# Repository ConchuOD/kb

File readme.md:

# Custom keyboard

Things that are sub-optimal:
- mounting holes are M2 when M3 would be better.
- SOD323 are needlessly small, requiring better soldering gear than is reasonable.

Thanks to Jorge Reyes for his simple T3.2 model: https://grabcad.com/library/teensy-3-1-3-2-1
Thanks also to Constantin for his eagle teensy models that I converted to use in kicad https://forum.pjrc.com/threads/24637-Updated-Teensy-3-1-and-Teensy-3-0-Eagle-libraries

After 2 years, I finally got myself a 3d printer. I might finally finish this :)

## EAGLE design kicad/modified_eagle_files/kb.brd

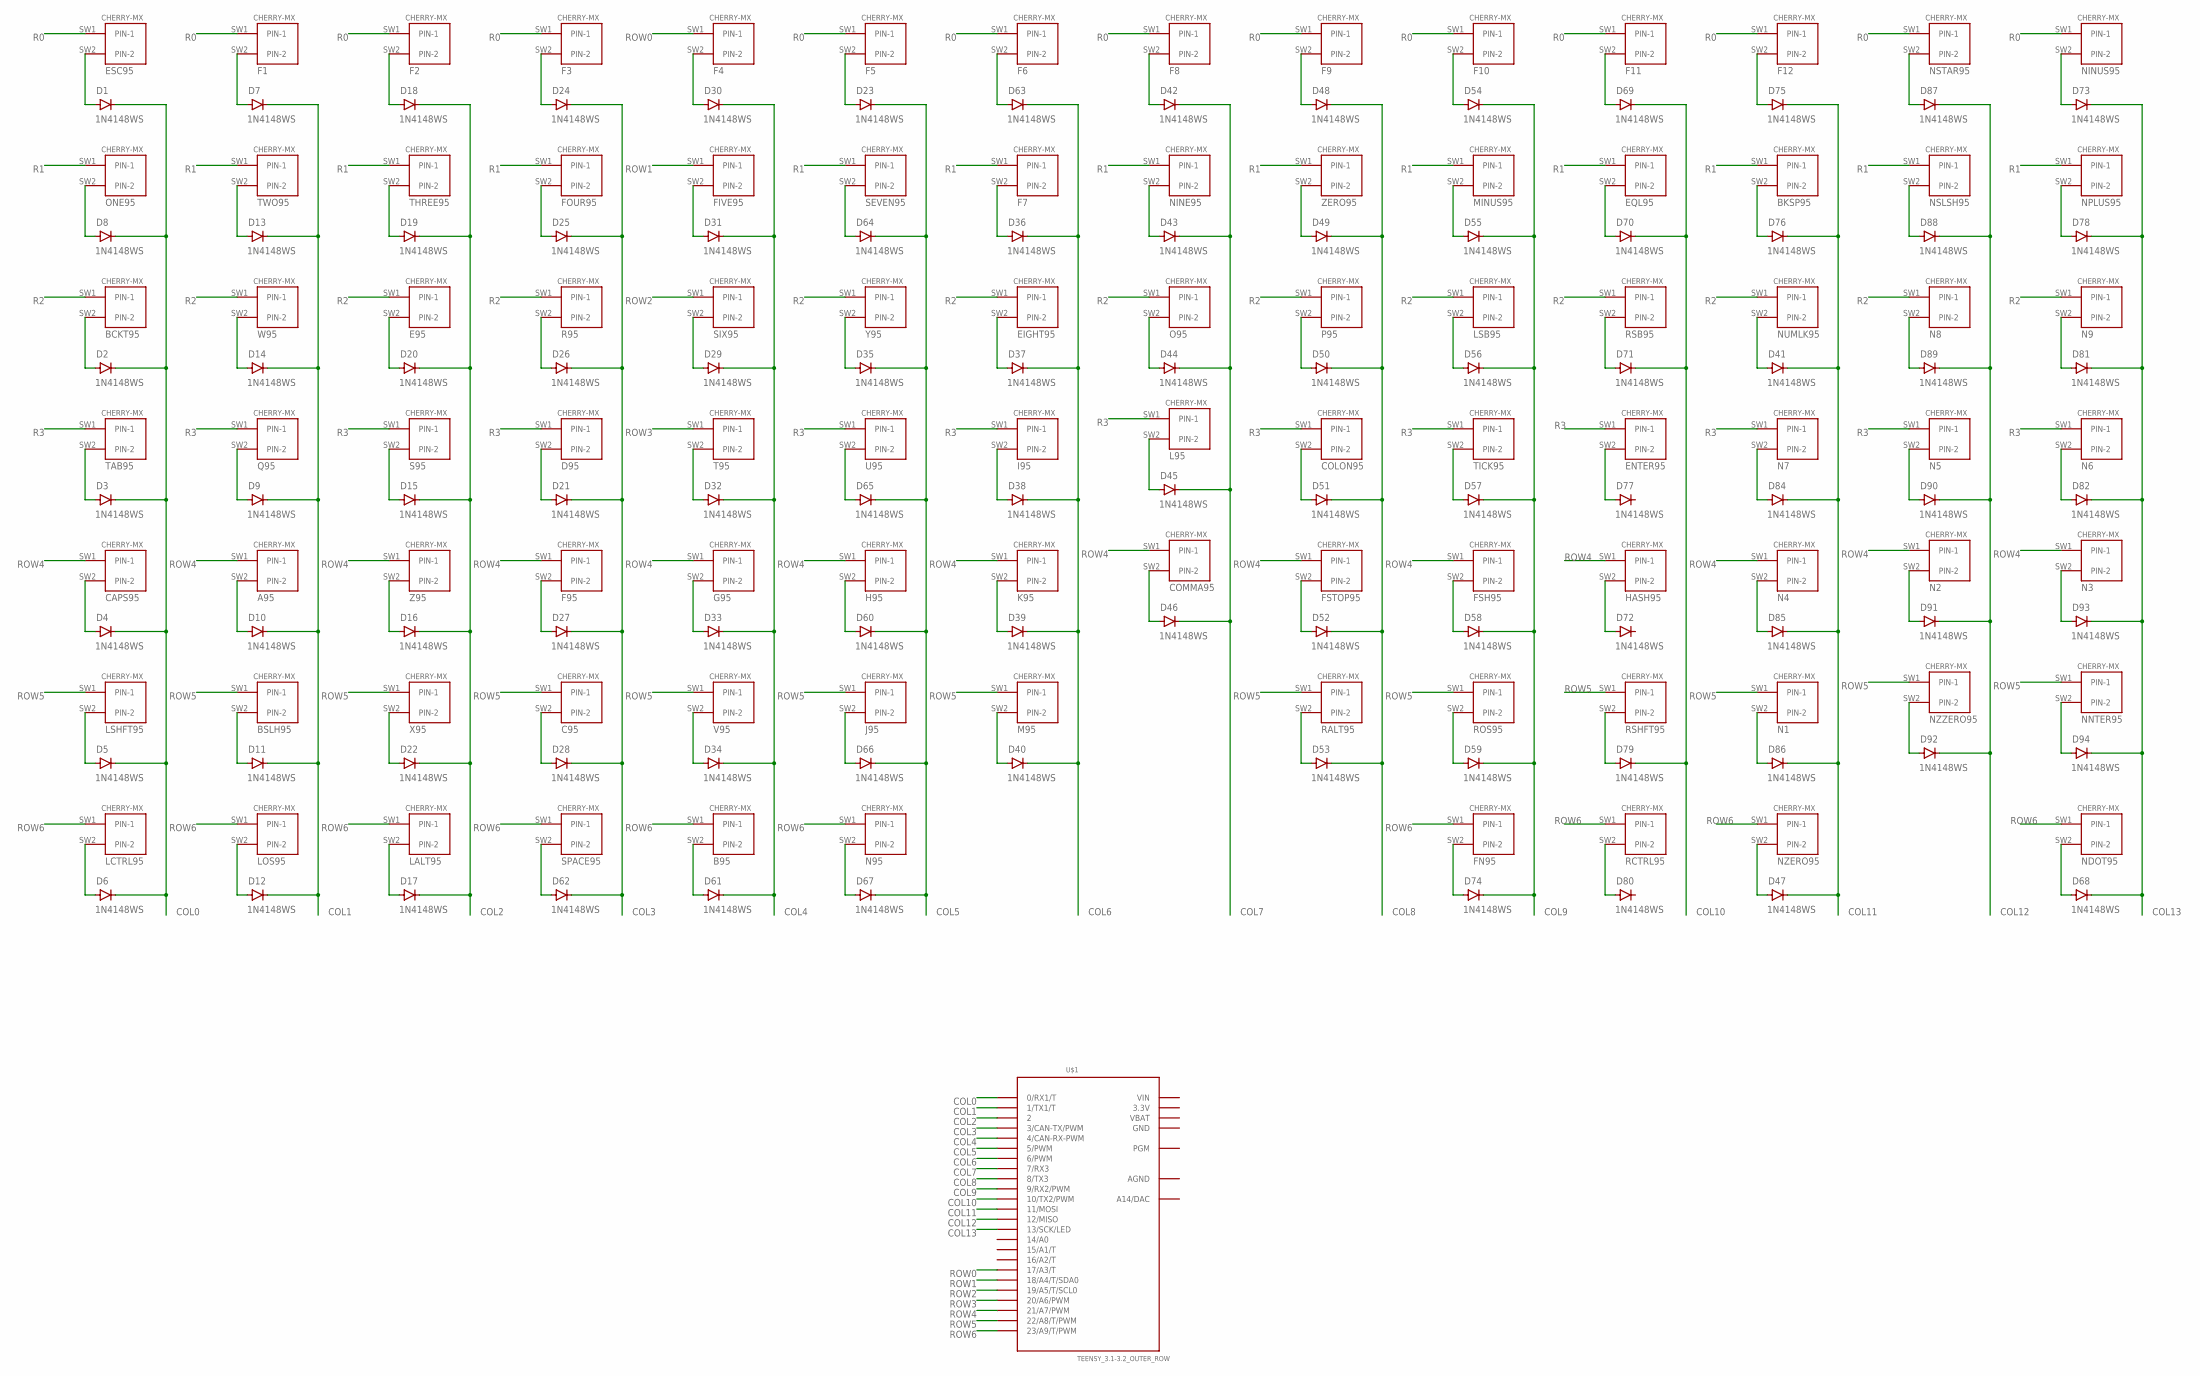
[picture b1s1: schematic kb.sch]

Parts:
A95: CHERRY-MX
B95: CHERRY-MX
BCKT95: CHERRY-MX
BKSP95: CHERRY-MX
BSLH95: CHERRY-MX
C95: CHERRY-MX
CAPS95: CHERRY-MX
COLON95: CHERRY-MX
COMMA95: CHERRY-MX
D1, D2, D3, D4, D5, D6, D7, D8, D9, D10, D11, D12, D13, D14, D15, D16, D17, D18, D19, D20, D21, D22, D23, D24, D25, D26, D27, D28, D29, D30, D31, D32, D33, D34, D35, D36, D37, D38, D39, D40, D41, D42, D43, D44, D45, D46, D47, D48, D49, D50, D51, D52, D53, D54, D55, D56, D57, D58, D59, D60, D61, D62, D63, D64, D65, D66, D67, D68, D69, D70, D71, D72, D73, D74, D75, D76, D77, D78, D79, D80, D81, D82, D84, D85, D86, D87, D88, D89, D90, D91, D92, D93, D94: 1N4148WS; SOD-323
D95: CHERRY-MX
E95: CHERRY-MX
EIGHT95: CHERRY-MX
ENTER95: CHERRY-MX
EQL95: CHERRY-MX
ESC95: CHERRY-MX
F1, F2, F3, F4, F5, F6, F7, F8, F9, F10, F11, F12, F95: CHERRY-MX
FIVE95: CHERRY-MX
FN95: CHERRY-MX
FOUR95: CHERRY-MX
FSH95: CHERRY-MX
FSTOP95: CHERRY-MX
G95: CHERRY-MX
H95: CHERRY-MX
HASH95: CHERRY-MX
I95: CHERRY-MX
J95: CHERRY-MX
K95: CHERRY-MX
L95: CHERRY-MX
LALT95: CHERRY-MX
LCTRL95: CHERRY-MX
LOS95: CHERRY-MX
LSB95: CHERRY-MX
LSHFT95: CHERRY-MX
M95: CHERRY-MX
MINUS95: CHERRY-MX
N1, N2, N3, N4, N5, N6, N7, N8, N9, N95: CHERRY-MX
NDOT95: CHERRY-MX
NINE95: CHERRY-MX
NINUS95: CHERRY-MX
NNTER95: CHERRY-MX
NPLUS95: CHERRY-MX
NSLSH95: CHERRY-MX
NSTAR95: CHERRY-MX
NUMLK95: CHERRY-MX
NZERO95: CHERRY-MX
NZZERO95: CHERRY-MX
O95: CHERRY-MX
ONE95: CHERRY-MX
P95: CHERRY-MX
Q95: CHERRY-MX
R95: CHERRY-MX
RALT95: CHERRY-MX
RCTRL95: CHERRY-MX
ROS95: CHERRY-MX
RSB95: CHERRY-MX
RSHFT95: CHERRY-MX
S95: CHERRY-MX
SEVEN95: CHERRY-MX
SIX95: CHERRY-MX
SPACE95: CHERRY-MX
T95: CHERRY-MX
TAB95: CHERRY-MX
THREE95: CHERRY-MX
TICK95: CHERRY-MX
TWO95: CHERRY-MX
U95: CHERRY-MX
U$1: TEENSY_3.1-3.2_OUTER_ROW; TEENSY_3.0-3.2&LC_OUTER_ROW
V95: CHERRY-MX
W95: CHERRY-MX
X95: CHERRY-MX
Y95: CHERRY-MX
Z95: CHERRY-MX
ZERO95: CHERRY-MX

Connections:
3.3V: U$1.3.3V, U$1.3.3V1 (3.3V)
AGND: U$1.AGND
COL0: D1.C, D2.C, D3.C, D4.C, D5.C, D6.C, D8.C, U$1.0 (0/RX1/T)
COL1: D7.C, D9.C, D10.C, D11.C, D12.C, D13.C, D14.C, U$1.1 (1/TX1/T)
COL2: D15.C, D16.C, D17.C, D18.C, D19.C, D20.C, D22.C, U$1.2
COL3: D21.C, D24.C, D25.C, D26.C, D27.C, D28.C, D62.C, U$1.3 (3/CAN-TX/PWM)
COL4: D29.C, D30.C, D31.C, D32.C, D33.C, D34.C, D61.C, U$1.4 (4/CAN-RX-PWM)
COL5: D23.C, D35.C, D60.C, D64.C, D65.C, D66.C, D67.C, U$1.5 (5/PWM)
COL6: D36.C, D37.C, D38.C, D39.C, D40.C, D63.C, U$1.6 (6/PWM)
COL7: D42.C, D43.C, D44.C, D45.C, D46.C, U$1.7 (7/RX3)
COL8: D48.C, D49.C, D50.C, D51.C, D52.C, D53.C, U$1.8 (8/TX3)
COL9: D54.C, D55.C, D56.C, D57.C, D58.C, D59.C, D74.C, U$1.9 (9/RX2/PWM)
COL10: D69.C, D70.C, D71.C, D79.C, U$1.10 (10/TX2/PWM)
COL11: D41.C, D47.C, D75.C, D76.C, D84.C, D85.C, D86.C, U$1.11 (11/MOSI)
COL12: D87.C, D88.C, D89.C, D90.C, D91.C, D92.C, U$1.12 (12/MISO)
COL13: D68.C, D73.C, D78.C, D81.C, D82.C, D93.C, D94.C, U$1.13 (13/SCK/LED)
GND: U$1.GND, U$1.GND1 (GND)
unnamed: D1.A, ESC95.SW2 (PIN-2)
unnamed: BCKT95.SW2 (PIN-2), D2.A
unnamed: D3.A, TAB95.SW2 (PIN-2)
unnamed: CAPS95.SW2 (PIN-2), D4.A
unnamed: D5.A, LSHFT95.SW2 (PIN-2)
unnamed: D6.A, LCTRL95.SW2 (PIN-2)
unnamed: D8.A, ONE95.SW2 (PIN-2)
unnamed: D9.A, Q95.SW2 (PIN-2)
unnamed: A95.SW2 (PIN-2), D10.A
unnamed: BSLH95.SW2 (PIN-2), D11.A
unnamed: D12.A, LOS95.SW2 (PIN-2)
unnamed: D13.A, TWO95.SW2 (PIN-2)
unnamed: D14.A, W95.SW2 (PIN-2)
unnamed: D15.A, S95.SW2 (PIN-2)
unnamed: D16.A, Z95.SW2 (PIN-2)
unnamed: D17.A, LALT95.SW2 (PIN-2)
unnamed: D7.A, F1.SW2 (PIN-2)
unnamed: D19.A, THREE95.SW2 (PIN-2)
unnamed: D20.A, E95.SW2 (PIN-2)
unnamed: D21.A, D95.SW2 (PIN-2)
unnamed: D22.A, X95.SW2 (PIN-2)
unnamed: D29.A, SIX95.SW2 (PIN-2)
unnamed: D18.A, F2.SW2 (PIN-2)
unnamed: D25.A, FOUR95.SW2 (PIN-2)
unnamed: D26.A, R95.SW2 (PIN-2)
unnamed: D27.A, F95.SW2 (PIN-2)
unnamed: C95.SW2 (PIN-2), D28.A
unnamed: D35.A, Y95.SW2 (PIN-2)
unnamed: D24.A, F3.SW2 (PIN-2)
unnamed: D31.A, FIVE95.SW2 (PIN-2)
unnamed: D32.A, T95.SW2 (PIN-2)
unnamed: D33.A, G95.SW2 (PIN-2)
unnamed: D34.A, V95.SW2 (PIN-2)
unnamed: D60.A, H95.SW2 (PIN-2)
unnamed: D30.A, F4.SW2 (PIN-2)
unnamed: D37.A, EIGHT95.SW2 (PIN-2)
unnamed: D38.A, I95.SW2 (PIN-2)
unnamed: D39.A, K95.SW2 (PIN-2)
unnamed: D40.A, M95.SW2 (PIN-2)
unnamed: D41.A, NUMLK95.SW2 (PIN-2)
unnamed: D36.A, F7.SW2 (PIN-2)
unnamed: D43.A, NINE95.SW2 (PIN-2)
unnamed: D44.A, O95.SW2 (PIN-2)
unnamed: D45.A, L95.SW2 (PIN-2)
unnamed: COMMA95.SW2 (PIN-2), D46.A
unnamed: D47.A, NZERO95.SW2 (PIN-2)
unnamed: D42.A, F8.SW2 (PIN-2)
unnamed: D49.A, ZERO95.SW2 (PIN-2)
unnamed: D50.A, P95.SW2 (PIN-2)
unnamed: COLON95.SW2 (PIN-2), D51.A
unnamed: D52.A, FSTOP95.SW2 (PIN-2)
unnamed: D53.A, RALT95.SW2 (PIN-2)
unnamed: D48.A, F9.SW2 (PIN-2)
unnamed: D55.A, MINUS95.SW2 (PIN-2)
unnamed: D56.A, LSB95.SW2 (PIN-2)
unnamed: D57.A, TICK95.SW2 (PIN-2)
unnamed: D58.A, FSH95.SW2 (PIN-2)
unnamed: D59.A, ROS95.SW2 (PIN-2)
unnamed: D54.A, F10.SW2 (PIN-2)
unnamed: B95.SW2 (PIN-2), D61.A
unnamed: D62.A, SPACE95.SW2 (PIN-2)
unnamed: D23.A, F5.SW2 (PIN-2)
unnamed: D64.A, SEVEN95.SW2 (PIN-2)
unnamed: D65.A, U95.SW2 (PIN-2)
unnamed: D66.A, J95.SW2 (PIN-2)
unnamed: D67.A, N95.SW2 (PIN-2)
unnamed: D68.A, NDOT95.SW2 (PIN-2)
unnamed: D63.A, F6.SW2 (PIN-2)
unnamed: D70.A, EQL95.SW2 (PIN-2)
unnamed: D71.A, RSB95.SW2 (PIN-2)
unnamed: D72.A, HASH95.SW2 (PIN-2)
unnamed: D78.A, NPLUS95.SW2 (PIN-2)
unnamed: D74.A, FN95.SW2 (PIN-2)
unnamed: D69.A, F11.SW2 (PIN-2)
unnamed: BKSP95.SW2 (PIN-2), D76.A
unnamed: D77.A, ENTER95.SW2 (PIN-2)
unnamed: D81.A, N9.SW2 (PIN-2)
unnamed: D79.A, RSHFT95.SW2 (PIN-2)
unnamed: D80.A, RCTRL95.SW2 (PIN-2)
unnamed: D75.A, F12.SW2 (PIN-2)
unnamed: D82.A, N6.SW2 (PIN-2)
unnamed: D84.A, N7.SW2 (PIN-2)
unnamed: D85.A, N4.SW2 (PIN-2)
unnamed: D86.A, N1.SW2 (PIN-2)
unnamed: D93.A, N3.SW2 (PIN-2)
unnamed: D88.A, NSLSH95.SW2 (PIN-2)
unnamed: D89.A, N8.SW2 (PIN-2)
unnamed: D90.A, N5.SW2 (PIN-2)
unnamed: D91.A, N2.SW2 (PIN-2)
unnamed: D92.A, NZZERO95.SW2 (PIN-2)
unnamed: D87.A, NSTAR95.SW2 (PIN-2)
unnamed: D94.A, NNTER95.SW2 (PIN-2)
unnamed: D73.A, NINUS95.SW2 (PIN-2)
R0: ESC95.SW1 (PIN-1), F1.SW1 (PIN-1), F2.SW1 (PIN-1), F3.SW1 (PIN-1), F5.SW1 (PIN-1), F6.SW1 (PIN-1), F8.SW1 (PIN-1), F9.SW1 (PIN-1), F10.SW1 (PIN-1), F11.SW1 (PIN-1), F12.SW1 (PIN-1), NINUS95.SW1 (PIN-1), NSTAR95.SW1 (PIN-1)
R1: BKSP95.SW1 (PIN-1), EQL95.SW1 (PIN-1), F7.SW1 (PIN-1), FOUR95.SW1 (PIN-1), MINUS95.SW1 (PIN-1), NINE95.SW1 (PIN-1), NPLUS95.SW1 (PIN-1), NSLSH95.SW1 (PIN-1), ONE95.SW1 (PIN-1), SEVEN95.SW1 (PIN-1), THREE95.SW1 (PIN-1), TWO95.SW1 (PIN-1), ZERO95.SW1 (PIN-1)
R2: BCKT95.SW1 (PIN-1), E95.SW1 (PIN-1), EIGHT95.SW1 (PIN-1), LSB95.SW1 (PIN-1), N8.SW1 (PIN-1), N9.SW1 (PIN-1), NUMLK95.SW1 (PIN-1), O95.SW1 (PIN-1), P95.SW1 (PIN-1), R95.SW1 (PIN-1), RSB95.SW1 (PIN-1), W95.SW1 (PIN-1), Y95.SW1 (PIN-1)
R3: COLON95.SW1 (PIN-1), D95.SW1 (PIN-1), ENTER95.SW1 (PIN-1), I95.SW1 (PIN-1), L95.SW1 (PIN-1), N5.SW1 (PIN-1), N6.SW1 (PIN-1), N7.SW1 (PIN-1), Q95.SW1 (PIN-1), S95.SW1 (PIN-1), TAB95.SW1 (PIN-1), TICK95.SW1 (PIN-1), U95.SW1 (PIN-1)
ROW0: F4.SW1 (PIN-1), U$1.17/A3 (17/A3/T)
ROW1: FIVE95.SW1 (PIN-1), U$1.18/A4 (18/A4/T/SDA0)
ROW2: SIX95.SW1 (PIN-1), U$1.19/A5 (19/A5/T/SCL0)
ROW3: T95.SW1 (PIN-1), U$1.20/A6 (20/A6/PWM)
ROW4: A95.SW1 (PIN-1), CAPS95.SW1 (PIN-1), COMMA95.SW1 (PIN-1), F95.SW1 (PIN-1), FSH95.SW1 (PIN-1), FSTOP95.SW1 (PIN-1), G95.SW1 (PIN-1), H95.SW1 (PIN-1), HASH95.SW1 (PIN-1), K95.SW1 (PIN-1), N2.SW1 (PIN-1), N3.SW1 (PIN-1), N4.SW1 (PIN-1), U$1.21/A7 (21/A7/PWM), Z95.SW1 (PIN-1)
ROW5: BSLH95.SW1 (PIN-1), C95.SW1 (PIN-1), J95.SW1 (PIN-1), LSHFT95.SW1 (PIN-1), M95.SW1 (PIN-1), N1.SW1 (PIN-1), NNTER95.SW1 (PIN-1), NZZERO95.SW1 (PIN-1), RALT95.SW1 (PIN-1), ROS95.SW1 (PIN-1), RSHFT95.SW1 (PIN-1), U$1.22/A8 (22/A8/T/PWM), V95.SW1 (PIN-1), X95.SW1 (PIN-1)
ROW6: B95.SW1 (PIN-1), FN95.SW1 (PIN-1), LALT95.SW1 (PIN-1), LCTRL95.SW1 (PIN-1), LOS95.SW1 (PIN-1), N95.SW1 (PIN-1), NDOT95.SW1 (PIN-1), NZERO95.SW1 (PIN-1), RCTRL95.SW1 (PIN-1), SPACE95.SW1 (PIN-1), U$1.23/A9 (23/A9/T/PWM)
VBAT: U$1.VBAT
VIN: U$1.VIN

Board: 2 copper layers, 187 parts (0 on the bottom side), 120 nets, no tracks yet.

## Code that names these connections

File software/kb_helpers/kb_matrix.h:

#ifndef KB_MATRIX_H_
#define KB_MATRIX_H_

#include <kinetis.h>
#include <Arduino.h>
#include "keycodes.h"

#define COL0_PIN  0
#define COL1_PIN  1
#define COL2_PIN  2
#define COL3_PIN  3
#define COL4_PIN  4
#define COL5_PIN  5
#define COL6_PIN  6
#define COL7_PIN  7
#define COL8_PIN  8
#define COL9_PIN  9
#define COL10_PIN 10
#define COL11_PIN 11
#define COL12_PIN 12
#define COL13_PIN 13

#define ROW0_PIN  17
#define ROW1_PIN  18
#define ROW2_PIN  19
#define ROW3_PIN  20
#define ROW4_PIN  21
#define ROW5_PIN  22
#define ROW6_PIN  23

#define NUM_ROWS  7
#define NUM_COLS  14

static const uint16_t matrix_to_keycode[NUM_ROWS * NUM_COLS] = {
    KC_ESC,   KC_ONE,   KC_BTK,   KC_TAB,    KC_CAPS,  KC_LSHFT, KC_LCTRL,
    KC_F1,    KC_TWO,   KC_W,     KC_Q,      KC_A,     KC_BSLH,  KC_LOS,
    KC_F2,    KC_THREE, KC_E,     KC_S,      KC_Z,     KC_X,     KC_LALT,
    KC_F3,    KC_FOUR,  KC_R,     KC_D,      KC_F,     KC_C,     KC_SPACE,
    KC_F4,    KC_FIVE,  KC_SIX,   KC_T,      KC_G,     KC_V,     KC_B,
    KC_F5,    KC_SEVEN, KC_Y,     KC_U,      KC_H,     KC_J,     KC_N,
    KC_F6,    KC_F7,    KC_EIGHT, KC_I,      KC_K,     KC_M,     0,
    KC_F8,    KC_NINE,  KC_O,     KC_L,      KC_COMMA, 0,        0,
    KC_F9,    KC_ZERO,  KC_P,     KC_SCOLON, KC_DOT,   KC_RALT,  0,
    KC_F10,   KC_MINUS, KC_LSB,   KC_TICK,   KC_FSLSH, KC_ROS,   KC_RCTRL,
    KC_F11,   KC_EQUAL, KC_RSB,   KC_ENTER,  KC_HASH,  KC_RSHFT, KC_RCTRL,
    KC_F12,   KC_BKSP,  KC_NUMLK, KC_N7,     KC_N4,    KC_N1,    KC_N0,
    KC_NSTAR, KC_NSLSH, KC_N8,    KC_N5,     KC_N2,    KC_N0,    0,
    KC_NINUS, KC_NPLUS, KC_N9,    KC_N6,     KC_N3,    KC_NNTER, KC_NDOT
};

void setup_teensy_ports(void);

#endif /* KB_MATRIX_H_ */

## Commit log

2019-11-25 initial commit for custom kb
2019-11-25 readme
2019-11-25 more routing
2019-11-28 routing done
2019-11-30 deleting unneeded files
2019-11-30 readme update for lib attribution
2019-12-01 ready for manuf.
2019-12-10 moving labels on T32
2019-12-11 updated ignores
2019-12-11 updating files based on new ignore
2019-12-11 kicad/ -> hardware/
2019-12-11 adding teensy cores submodule
2019-12-11 initial commit on software side of things. Spent today setting up vscode and creating some (unlikely to compile) test code.
2019-12-11 attempting to make cores submodule track master directly
2019-12-13 builds at least
2019-12-13 makefile: -std=c11
2019-12-13 makefile: make clean updated to remove every leftover object
2019-12-15 validity of keyboard matrix confirmed
2019-12-16 working on matrix to LUT
2019-12-16 spitting letters into serial console
2019-12-17 preprocessor LUT for keycodes
2019-12-17 Disabling usb serial
2019-12-17 properly deleting objects etc
2019-12-17 pending exposal of keycode related functions to avoid pjrc supplied unicode based stuff - just do my own extention of stream
2019-12-18 now spitting out keys into terminal
2019-12-20 initial modifier handling
2019-12-21 repeat rate sorted. no modifiers. 1kro :joy:
2019-12-21 send via system (wrapped in IntervalTimer)
2019-12-22 20kro
2019-12-22 modifiers (and its 6kro over usb not 20)
2020-01-05 now working on windows and dupliate polling removed
2020-01-05 update tcores and rename files to avoid conflict with tcores provided usb keyboard
2022-02-17 2 years later...
2022-05-22 Create LICENSE
